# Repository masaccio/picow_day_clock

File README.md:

# Raspberry Pi Pico Day of Week Clock

## Current status

This project **is a work in progress**.

The clock is now feature complete from a software perspective though if this were scaled up for sale, it would need user-level configuration using a Wi-Fi connection and a web-server to provide the credentials and would also need some means of initiating a factory reset. Better still would be bluetooth discovery from a phone app to configure the clock for things like timezones, colors and fonts as well as the Wi-Fi credentials. The clock build looks like this:

Next steps in the project are:

* Move away from the Waveshare LCD as they are quite bulky despite my surgery and I now plan to build my own backlight circuitry and drive a bare LCD
* Add a factory reset button to the design (software is complete)
* Add an alarm LED to the design for terminal failure of the LCDs or any other unrecoverable fault
* Design a 2-layer PCB to host the design as the current soldered design is too fragile
* Build a walnut enclosure

## Introduction

This project is the software, hardware design and clock enclosure design for an LCD clock driven by the Raspberry Pi Pico 2 W. The clock design is inspired by the idea of a [Nixie](https://en.wikipedia.org/wiki/Nixie_tube) clock but uses LCDs so that the display is brighter and clearly visible in daylight. The clock is intended to be wall-mounted so the read is left a little messy to simplify the electronics build.

The project is *not* compatible with earlier versions of the Pico and requires the CYW43439 Wi-Fi chip present in the Pico 2 W to function correctly.

## Software Operation

The pin-out and Wi-Fi settings are hard-coded into the project at build time. After the Pico firmware boots, the software will:

* Initialize all 7 LCD modules writing to the UART and exiting if this fails
* Create a Wi-Fi connection to the hard-coded Wi-Fi network
* Get the current time from public NTP servers
* Display the abbreviated day of week on the first three LCDs and the current time in hours in minutes on the remaining 4 displays

NTP syncs start at once per day and respect back-off requests from the server if this is too frequent. The timer itself runs once per second and any NTP drift that occurs daily is compensated for in these timer callbacks.

### Diagnostics

A watchdog timer runs on the clock and reboots the Pico if there is no activity for `WATCHDOG_TIMEOUT_MS` which is 3 seconds by default. On reboot, the clock reconnects to Wi-Fi and resyncs with NTP.

The clock displays icons along the top edge of LCD1 when errors occur. The icons indicate watchdog status, NTP status and Wi-Fi status. They are coloured red for errors and green for normal status and indicate the nature of the error that occurred such as a Wi-Fi authentication problem or network timeout.

If the LCD cannot be initialized, the clock prints diagnostics to `stdout` as a last resort.

### Timezones and Daylight Saving Time

The software takes into consideration daylight saving time (DST) and timezones as configured in flash. Timezones are configured as hour/half-hour offsets matching those known across the globe. The following DST rules are available which covers all regions:

| Region / Pattern | DST Start Rule (Clocks go forward) | DST End Rule (Clocks go back) | Shift |
| --- | --- | --- | --- |
| **None** (Japan, India, Arizona, Hawaii) | *Does not observe DST* | *Does not observe DST* | 0 |
| **North America** (US, Canada) | 2nd Sunday in March at 02:00 | 1st Sunday in November at 02:00 | +1 Hour |
| **Europe / UK** (EU, UK, Switzerland) | Last Sunday in March at 01:00 UTC | Last Sunday in October at 01:00 UTC | +1 Hour |
| **Australia** (Most states) | 1st Sunday in October at 02:00 | 1st Sunday in April at 03:00 | +1 Hour |
| **New Zealand** | Last Sunday in September at 02:00 | 1st Sunday in April at 03:00 | +1 Hour |
| **Chile** | 1st Saturday in September at 24:00 | 1st Saturday in April at 24:00 | +1 Hour |
| **Israel** | Friday before the last Sunday in March | Last Sunday in October at 02:00 | +1 Hour |

## Configuration

Configuration is stored in Flash and the clock will reconfigure itself when:

* an invalid configuration is detected in flash
* the factory reset button is held for 3 seconds during boot
* the factory reset button is held for 3 seconds normal operation

If factory reset is hed during boot, the clock will erase the stored flash configuration regardless of whether it is valid or not making holding the reset during normal operation harmless until the configuration is saved.

During configuration, the clock starts a Wi-Fi access point with the prefix `Pico-Day-Clock-Setup` and the last part of the Pico's MAC address. Connecting a device to this Wi-Fi network should start a captive portal, but if not, the clock's default IP address is `192.168.4.1` and you can direct your browser to `http://192.168.4.1/`. The following form configures the clock:

The minimum setup is a valid Wi-Fi SSID and password. If the password is incorrect, you must force a factory reset as the clock will try indefinitely to connect to the configured Wi-Fi.

## Build and Testing

The software is expected to build on Mac, Linux and Windows hosts and should be able to be imported into the Raspberry Pi Pico extension to Visual Studio Code. The Pico target build uses the standard Pico SDK tooling, but the native tests and coverage require LLVM for Clang and the coverage tools.

Tests for the core clock functionality and error handling is largely complete through some very basic mocking of the Pico SDK. The [code](tests/mock.c) for the mocking is by no means complete and is just the very minimum required to make the clock function and generate errors that might occur such as DNS timeouts.

The tests run on the host and assume Clang is available. **Windows hosts are unsupported for testing** as the host implementation of `time_t` is incompatible with the NTP implementation which assumes uses timestamps starting in 1900 and in turn this requires 64-bit `time_t`.

Automated CI is provided by [GitHub runners](.github/workflows/build.yml).

## Debug

On boot, all LCDs are initialized first and diagnostic messages are displayed on the LCD1 as Wi-Fi and then NTP is initialized. On success, the clock starts. If any error is unrecoverable, signaled by a status message in red, the clock will not start and the diagnostics will remain. If the diagnostics do not appear at all, there is a problem with the LCD connections or the LCD driver. The following CMake configuration is available for debug to the UART:

* `CLOCK_DEBUG_ENABLED`: debug messages from the day of week clock itself
* `PICO_CYW43_ARCH_DEBUG_ENABLED`: SDK built-in debug of Wi-FI connections
* `LWIP_MALLOC_DEBUG`: SDK built-in memory allocation debug
* `LWIP_PROTOCOL_DEBUG`: SDK built-in UDP debug

## Pico pinout

The pinout for the LCD is defined in `config.h` using a series of C macros `LCD1_GPIO_xxx`. The backlight is shared across all of the LCDs as there is no need to control the dimming of the LCDs individually.

| Pin to device mapping    | Name      | Pin | Pico  | Pin | Name      | Pin to device mapping   |
|--------------------------|-----------|-----| ----- |-----|-----------|-------------------------|
| Debug Probe RX           | GP0       | 1   | XXXXX | 40  | VBUS 5V   |                         |
| Debug Probe TX           | GP1       | 2   | XXXXX | 39  | VSYS 5V   | DollaTek VIN            |
| Debug Probe GND          | GND       | 3   | XXXXX | 38  | GND       | LCD GND                 |
| LCD 1 chip select (CS)   | GP2       | 4   | XXXXX | 37  | 3V3 En    |                         |
| LCD 2 chip select (CS)   | GP3       | 5   | XXXXX | 36  | 3V3 Out   |                         |
| LCD 3 chip select (CS)   | GP4       | 6   | XXXXX | 35  | ADC VRef  |                         |
| LCD 4 chip select (CS)   | GP5       | 7   | XXXXX | 34  | GP28 A2   |                         |
|                          | GND       | 8   | XXXXX | 33  | ADC Gnd   |                         |
| LCD 5 chip select (CS)   | GP6       | 9   | XXXXX | 32  | GP27 A1   |                         |
| LCD 6 chip select (CS)   | GP7       | 10  | XXXXX | 31  | GP26 A0   |                         |
| LCD 7 chip select (CS)   | GP8       | 11  | XXXXX | 30  | RUN       |                         |
| Factory reset            | GP9       | 12  | XXXXX | 29  | GP22      |                         |
|                          | GND       | 13  | XXXXX | 28  | GND       |                         |
| Shared clock (CLK)       | GP10      | 14  | XXXXX | 27  | GP21      |                         |
| Shared MOSI (DIN)        | GP11      | 15  | XXXXX | 26  | GP20      |                         |
| Shared reset (RST)       | GP12      | 16  | XXXXX | 25  | GP19      |                         |
| Shared backlight (BL)    | GP13      | 17  | XXXXX | 24  | GP18      |                         |
|                          | GND       | 18  | XXXXX | 23  | GND       |                         |
| Shared data/command (DC) | GP14      | 19  | XXXXX | 22  | GP17      |                         |
| Diagnostic LED           | GP15      | 20  | XXXXX | 21  | GP16      |                         |

## Electrical Design

The LCD module expects a 3.3V supply and the [datasheet for the Waveshare 1.47inch LCD](https://files.waveshare.com/upload/9/99/1.47inch_LCD_Datasheet.pdf) indicates that the backlight draws 60-90mA. All the LCDs can therefore be driven by a single voltage regulator such as the DollaTek 1117:

* VIN: 5V VSYS from the USB power supply shared with the Pico
* VOUT: LCD VCC, shared across all LCD modules
* GND: any GND pin on the Pico

The BL backlight pin of the LCD module is not the actual  LCD backlight; it is a control pin to the LCD module's TXB0108PWR level shifter so can also be shared across all LCDs and, like the other control signals, driven directly from the Pico.

The Pico has insufficient drive strength to drive the control signals of 7 LCDs simultaneously, so a logic level converter with the VA and VB tied to 3V3 is used to increase the drive strength and buffer between the Pico and the LCDs. Care must be taken to choose a level shift with sufficient drive strength; a single TXB0108 proved insufficient and the final design uses two four-channel Gebildet CYT1076 level shifters. One CYT1076 drives the day of week LCDs (LCD1-3) and the other the time LCDs (LCD4-7).

## Mechanical design

I chose the Waveshare LCD because it comes with a socket that has a wired plug with 2.54mm pin connectors for easy prototyping. For the final clock, this connector gets in the way of the wires hiding neatly behind the LCD. There are 172x320 LCD displays that are based on the ST7789 that come with an FPC connector which is neatly connected on the narrow edge of the display. The bare LCD with the FPC connector has the disadvantage for the hobbyist that you need to add a ZIF socket and then break that out into something with a wider pitch to solder. The connector on the Waveshare board can be desoldered using solder braid and the connector carefully snipped off using flush snippers. The Waveshare module also has 2mm brass mounting holes which makes mounting the LCDs securely simpler. The main drawback of the approach is that the read of the LCD is quite messy, but the intended use is for a wall-mounted clock. The soldered connections look like this (please forgive the terrible soldering skills; I am out of practice):

The glass domes appear to be referred to as "glass dome cloche covers with cork bases" and are available from Chinese manufactures on sites like [TEMU](https://www.temu.com/). Since the class is reasonably heavy 2mm thick glass, the 25mm domes are too narrow in the internal diameter for the LCD so 28mm domes are required. Unfortunately 71mm long so they need to sit about 25mm below the top of the clock so that the LCDs are comfortable in the upper section of the dome. The domes sit inside a 4mm brass frame to which the LCDs can be held using M2 machine screws:

The brass frame is laser cut from 4mm brass using a CAD file that is generated using `scripts/generate-dxf.py`. Assuming CMake has generated the Python virtual environment in the `build` folder, you can build the DXF file (`generated/clock_brass.dxf`) using:

``` bash
source build/scripts_venv/bin/activate
pip install ezdxf
python3 scripts/create-cad-drawing.py
```

It's also possible to generate a 3D model using Python for use as a 3D printing prototype to check that that everything aligns correctly:

``` bash
source build/scripts_venv/bin/activate
pip install cadquery cadquery-ocp
python3 scripts/create-3d-model.py
```

The brass frame is then sandwiched between two rectangular woden boxes with no lids. The USB power cable is fed through one box and plugs into the Pico's USB port which simplifies the electrical design.

## Credits

ST7789 init and driver code is derived from the [Waveshare Sample Demo](https://www.waveshare.com/wiki/1.47inch_LCD_Module) for the Waveshare 1.47inch LCD. The driver is [licensed](licenses/waveshare.txt) by the Waveshare team under an MIT license.

NTP driver code is derived from [pico_ntp_client](https://github.com/raspberrypi/pico-examples/tree/master/pico_w/wifi/ntp_client) in the [Raspberry Pi Pico SDK Examples](https://github.com/raspberrypi/pico-examples) which is [licensed](raspberry-pi.txt) under a BSD license.

The access point and associated DHCP/DNS server are derived from [pico_access_point](https://github.com/raspberrypi/pico-examples/tree/master/pico_w/wifi/access_point) in the [Raspberry Pi Pico SDK Examples](https://github.com/raspberrypi/pico-examples) which is [licensed](raspberry-pi.txt) under a BSD license.

Variable width fonts replace the fixed-width fonts in the Waveshare examples, but the C data structures are ultimately derived from work by STMicroelectronics [licensed](licenses/stm.txt) under the 3-clause BSD license.

The digit fonts included in the repository are [Bebas Neue Regular](https://fonts.google.com/specimen/Bebas+Neue) which is [licensed](licenses/BebasNeue-OFL.txt) under the Open Font License, and [Oswald](https://fonts.google.com/specimen/Oswald) which is also [licensed](licenses/Oswald-OFL.txt) under the Open Font License.

The text font used in display diagnostics during boot is [Roboto Medium](https://fonts.google.com/specimen/Roboto) which is [licensed](licenses/Roboto-OFL.txt) under the Open Font License.

Icons in this project are derived from [Google Material Design Icons](https://github.com/google/material-design-icons), which are licensed under the [Apache License 2.0](https://github.com/google/material-design-icons/blob/master/LICENSE). The icons have been resized and converted to C bitmaps for use in this project, and new icons have been derived to addition status badges.

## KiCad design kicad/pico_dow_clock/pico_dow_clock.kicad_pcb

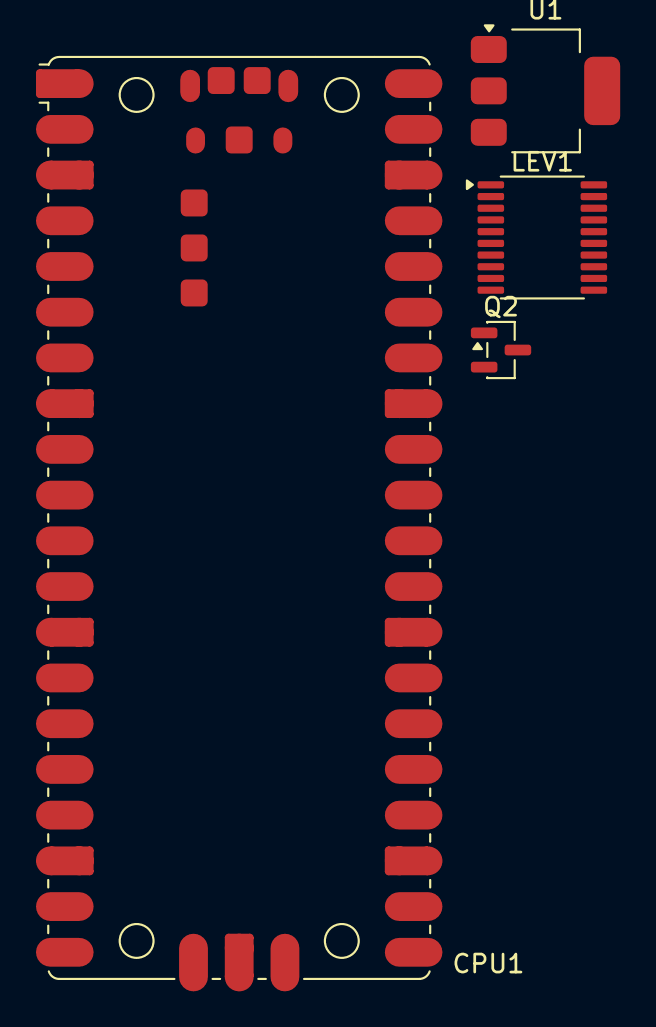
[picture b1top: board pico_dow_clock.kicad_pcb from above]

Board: 2 copper layers, 4 parts (0 on the bottom side), 9 nets, no tracks yet.

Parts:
CPU1: RaspberryPi_Pico; RaspberryPi_Pico_Original_SMD
LEV1: SN74LVC245N; TSSOP-20_4.4x6.5mm_P0.65mm
Q2: AO3400A; SOT-23
U1: AMS1117-3.3; SOT-223-3_TabPin2

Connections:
+3.3V: LEV1.1 (DIR), LEV1.20 (VCC), U1.2 (VO)
/LCD_BL: CPU1.17 (GPIO13), Q2.1 (G)
/P_LCD_CLK: CPU1.14 (GPIO10), LEV1.4 (A3)
/P_LCD_DC: CPU1.19 (GPIO14), LEV1.5 (A4)
/P_LCD_DIN: CPU1.15 (GPIO11), LEV1.3 (A2)
/P_LCD_RST: CPU1.16 (GPIO12), LEV1.2 (A1)
GND: CPU1.TP1 (USB_GND), LEV1.10 (GND), LEV1.19 (~OE), Q2.2 (S), U1.1 (GND)
unnamed: LEV1.6 (A5), LEV1.7 (A6), LEV1.8 (A7), LEV1.9 (A8)
VBUS: CPU1.40 (VBUS), U1.3 (VI)

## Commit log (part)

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2025-09-13 Optional GNU coverage flags
2025-09-13 Single line CMake to keep Windows happy
2025-09-14 Fixing compile flags
2025-09-14 Reference pico-sdk in subdirectory
2025-09-14 Fix missing quote
2025-09-14 Use the correct target link libraries for Linux
2025-09-14 Added gcc coverage option
2025-09-14 Use GCC coverage on Ubuntu
2025-09-14 Install lcov on Ubuntu
2025-09-14 Make Ninja verbose
2025-09-14 Windows-friendly python choice
2025-09-14 Fix broken lcov commands
2025-09-14 Fix lcov 'Extra parameter found' error
2025-09-14 Move --branch-coverage to capture
2025-09-14 Clean up lcov command line
2025-09-14 Remove use of touch for dependencies
2025-09-14 Test WIndows paths for fontgen
2025-09-14 Dump platform vars
2025-09-14 Use pre-installed cmake and ninja
2025-09-14 Test CMAKE_SYSTEM_NAME for Windows
2025-09-14 Windows runner debugging
2025-09-14 More host debugging
2025-09-14 Remove debug code for Windows testing
2025-09-14 ENable test builds on Windows
2025-09-14 Test debug for Windows
2025-09-14 Debug Windows test run
2025-09-14 More Windows debug
2025-09-14 Remove MSVC flags
2025-09-15 Switch all native tests to Clang
2025-09-15 Remove LLVM_TOOLCHAIN_PATH
2025-09-15 Initial draft of full readme with licenses.
2025-09-15 Define GPIO pins in header
2025-09-15 Try clang rather than clang-cl for Windows
2025-09-15 Start electrical docs
2025-09-15 Remove dead code
2025-09-15 Add Windows gettimeofday
2025-09-15 struct timeval for WIN32
2025-09-15 struct timeval in clock.h
2025-09-15 Disable Windows secure CRT warnings
2025-09-15 Debugging Windows builds
2025-09-15 Fixing timeval errors
2025-09-16 Discard debug pragma
2025-09-16 Added schematic diagram
2025-09-16 Moving image location
2025-09-16 Correct LCD6/7 CS/DC
2025-09-16 Fix URL to schematic
2025-09-16 Lots about the TI buffer chip
2025-09-16 Fix schematic paths
2025-09-16 Rename secrets to config.cmake
2025-09-16 Rename secrets.cmake
2025-09-16 Document configuration
2025-09-16 Tweak config macros
2025-09-16 Fix CS wiring
2025-09-16 Fix filename
2025-09-16 Updated license information
2025-09-16 Replacing copyright comments with README
2025-09-16 Add note about timezones.
2025-09-16 Fix NTP DNS lookup error handling
2025-09-16 DNS timeout/failure tests
2025-09-16 Test handling of additional NTP errors
2025-09-16 Test time_as_string()
2025-09-16 last_day_of_month coverage
2025-09-17 Remove debug to main and add Attach to Pico
2025-09-17 Note about LLVM requirement
2025-09-17 Ignore log files
2025-09-17 Revert to local build folder
2025-09-17 Moving fonts into fonts/ and making scripts location generic
2025-09-17 Add watchdog and icons
2025-09-17 Add watchdog support
2025-09-17 Clearer comments
2025-09-17 MOve icon code to lcd_update_icon() and use std types
2025-09-18 Adding python doc
2025-09-18 Fix MSB encoding
2025-09-18 Fix icon pointers and remove DNS
2025-09-18 Disable LWIP debug
2025-09-18 Remove DNS icon
2025-09-18 Mock watchdog_reboot()
2025-09-18 Use uint8_t* for image
2025-09-18 Kick watchdog when fetching NTP
2025-09-18 Handle watchdog reset and switch to using red/green icons
2025-09-18 Use non-zero default reset reason
2025-09-18 Remove uncessary intermediate
2025-09-18 Fix clobbering of gmtime() buffer
2025-09-19 Added python icon script target
2025-09-19 Fix JSON
2025-09-19 Add credit for icons
2025-09-19 More consistent naming
2025-09-19 Switch to more expressive icons
2025-09-19 No longer required
2025-09-19 Re-added default NTP and Wi-Fi icons
2025-09-19 Moved generic status into status.h
2025-09-19 Adjust icon offsets
2025-09-19 Display watchdog icon state
2025-09-19 Document clock icons
2025-09-19 Handle test mode icon updates in fatal error
2025-09-19 Clean up untidy icon case/switch
2025-09-19 Improve test log output and switch to icons
2025-09-20 Disable CYW43 debug
2025-09-20 Clock debug timer simplified
2025-09-20 Initial prototype
2025-09-20 Document prototype status
2025-09-20 Reduce size
2025-09-20 Fix image URLs
2025-09-20 Further URL fixes
2025-09-21 Initial thoughts on mechanical design of the LCD connector.
2025-09-21 Move tests from src/
2025-09-21 Test NTP bad response and KoD
2025-09-22 Add branch % to HTML coverage
2025-09-22 Additional NTP coverage
2025-09-22 disconnect_from_wifi never used
2025-09-22 Tweak summary information for coverage
2025-09-22 UDP protocol error coverage
2025-09-22 Additional watchdog coverage tests
2025-09-22 POSIX time definitions for Windows
2025-09-22 Fix broken preprocessor definitions
2025-09-22 Try clang-cl
2025-09-23 Added clean and removed unnecessary ALL
2025-09-23 Ensure all targets depend upon icons and fonts
2025-09-23 Additional comments
2025-09-23 Clean up passing of compilers from top-level
2025-09-23 Clean Pillow
2025-09-23 Note that TXB0108 is likely unsuitable
2025-09-23 Start moving config to config.h and consolidating headers
2025-09-23 Move contents of ntp.h into clock.h
2025-09-23 Remove display rotation code
2025-09-23 Latest status updates for project
2025-09-23 Define CXX compile to stop CMake complaining about different compilers
2025-09-23 Change config header
2025-09-23 Renaming LCD heigh and width for clarity
2025-09-23 Remove dead function prototype
2025-09-23 Document new level shifter
2025-09-23 Typo
2025-09-23 Latest layout
2025-09-25 Remove frame buffer code and write direct to ST7789
2025-09-25 Kick watchdog while waiting
2025-09-25 Fix icon position w/o frame buffer
2025-09-25 More diagnostics on first boot
2025-11-18 Switch clock to lower case weekdays
2025-11-18 Switch to lower case weekdays
2025-11-18 Ensure timeouts are shorter than watchdog
2025-11-18 Additional font notice
2025-12-10 Fix log error padding and adjust test for new NTP timeout
2025-12-10 New custom cSpell dictionary
2025-12-10 Fix typos
2025-12-10 New watchdog reboot icons
2025-12-10 Change watchdog icon on reboot
2025-12-11 -Wpedantic changes
2025-12-11 Verbose warnings
2025-12-11 Additional custom words
2025-12-12 -Wpedantic changes for types
2025-12-12 Fix alignment of glyph table pointer
2025-12-12 Additional Cmake keywords
2025-12-12 Generate named structs
2025-12-12 Use test build for pedantic compiler warnings
2025-12-12 Cleanups for pedantic compiler warnings
2025-12-12 Fix drift calculation regression
2025-12-12 Enable build type switch
2025-12-12 Enable USB stdio on release build
2025-12-12 Linux/Windows build errors
2025-12-12 Handle struct timeval differences on Windows
2025-12-12 Correct timeval test
2025-12-12 Put timeval code in set_time_of_day()
2025-12-12 More Windows timeval experiments
2025-12-12 More Windows experiments in types
2025-12-12 Debugging Windows build
2025-12-12 And another Windows test
2025-12-13 Correctly handle NTP error icon in normal operation
2025-12-14 Fix incremental rebuild
2025-12-14 Additional Cmake words
2025-12-14 More sensible NTP state in debug
2025-12-14 Detect watchdog resets
2025-12-14 Run back through main as far as detecting a watchdog reset
2025-12-14 Removed non-return codes from state enum in favour of flags
2025-12-14 Moved watchdog error icons into a separate state
2025-12-14 Allow semicolon after macro
2025-12-14 Test invalid UDP address returned
2025-12-14 time_is_dst() coverage tests
2025-12-15 Clearer Wi-Fi error names
2025-12-15 Separate out NTP status and NTP error enums
2025-12-15 Icon updates are now all at once
2025-12-15 Refactor watchdog status to alow icon to linger
2025-12-15 Removed dead status print code
2025-12-15 Print failures in time tests
2025-12-15 More debug
2025-12-15 Backing out debug code
2025-12-15 Lots of debug
2025-12-15 Correct debug print types
2025-12-15 Updated status to reflect current Windows build
2025-12-16 Removing Windows hosted test builds
2025-12-16 Notes in Windows tests
2025-12-16 Additional commands
2025-12-16 Cleaning up makefile
2025-12-16 Notes about Windows builds
2025-12-17 Larger 1024 px version
2025-12-17 New notes on mechanical design
2025-12-17 Fix URL typo
2025-12-17 Updated prototype status
2025-12-17 Removed planned work notes.
2025-12-17 Notes about generating CAD drawing
2025-12-18 Fix pitch calculations for total size
2025-12-18 Added STL script command-line.
2025-12-18 Simplified comments
2026-01-01 Add tab to mount LCD on
2026-01-01 Fixed image crop
2026-01-02 Clearer dimensions and labels
2026-01-02 Fix type errors
2026-01-02 Fix STL instructions
2026-01-02 Python path
2026-01-02 Additional words
2026-01-18 Minor readability changes
2026-01-23 Remove Pillow deprecation warning
2026-01-23 Remove all lcd.c from tests
2026-01-23 Fix test build dependency
2026-01-23 Always update mock icons to facilitate testing of icon reset
2026-01-24 Fix comment typo
2026-01-24 Add -verbose
2026-01-24 Check NTP error flag resets
2026-06-13 Added access point example code for configuration
2026-06-13 Added GPIO button to force configuration
2026-06-13 Initial boilerplate pages for clock config
2026-06-14 Don't leave in git (generated)
2026-06-14 Missing gpio_pull_up
2026-06-14 Minor formatting fixes
2026-06-14 Add generated HTML blob
2026-06-14 Generate a hex array
2026-06-14 No longer generated
2026-06-14 Service generated html bytes
2026-06-14 Robustness and parameter parsing for tcp_server_recv()
2026-06-18 Fix header and body parsing for POST
2026-06-18 Store config to flash
2026-06-18 Fixed config store
2026-06-19 Timezone and DST awareness
2026-06-19 Mock flash functions
2026-06-19 Improved DST tests
2026-06-19 Fix multiple wi-fi init bug
2026-06-20 Fixing test build
2026-06-20 Mock wifi server functions
2026-06-20 Ensure mock_tcp_server_state is set up
2026-06-20 Cleaner test macro and initial Wi-Fi AP tests
2026-06-20 mock_tcp_server_state added
2026-06-20 Fix AP tests
2026-06-20 Fix Wi-Fi AP test message
2026-06-21 Expose flash config in main clock to test harness
2026-06-21 Additional Wi-Fi AP tests
2026-06-22 Use #pragma once
2026-06-22 Migrate test config to mock_context_t
2026-06-22 KiCad ignores
2026-06-22 Fix mac size overflow bug
2026-06-22 Enable address sanitizer
2026-06-22 Refactoring test context
2026-06-23 Refactor test config for robustness removing log checks
2026-06-24 Refactoring main into separate modules to reduce conditional code
2026-06-24 Added example of LED flash
2026-06-24 Exclude test_main.c from Pico build
2026-06-24 Fixing address sanitizer memory leaks (Linux)
2026-06-24 Fix memory leak of state in free_memory()
2026-06-24 Added mock leak checker
2026-06-24 Small robustness and readability changes
2026-06-24 More memory leak fixes
2026-06-24 NTP epoch support
2026-06-26 Better test printf
2026-06-26 Don't slew large NTP drifts
2026-06-26 Use strtok_r() instead of strtok()
2026-06-26 Move away from deprecated methods
2026-06-26 Fix build options for tests
2026-06-26 Handle immediate need to update display on large drift
2026-06-26 Cleaning up NTP test code
2026-06-26 Ensure test files are found
2026-06-26 Handle unsynchronized leap indicator
2026-06-27 Move Wi-Fi AP structs to clock.h
2026-06-28 Remove static NTP and Wi-Fi settings from the Pico build of the clock
2026-06-28 Added next steps
2026-06-28 Appropriate use of atomics
2026-06-28 New clock loops
2026-06-29 Clarify timeout intent
2026-06-29 Fix factory reset timing on boot
2026-06-29 Remove dead config
2026-06-29 Fix use after free
2026-06-29 Leaks fail the tests
2026-06-29 NTP timeout wired from form
2026-06-29 Correct add_repeating_timer_ms return value
2026-06-29 Move volatile globals to state
2026-06-29 Localising status string code
2026-06-29 Removing more globals
2026-06-29 Fixed missing fieldset close
